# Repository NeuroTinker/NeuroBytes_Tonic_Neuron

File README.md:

# NeuroBytes Tonic Neuron

The NeuroBytes Tonic Neuron is an open-source hardware neuron simulator designed and sold by [NeuroTinker, LLC](http://www.neurotinker.com/). 

All NeuroBytes products are based on the ST32L0x series of ARM Cortex-M0+ 32-bit microcontrollers. The boards were designed in KiCad and Inkscape and are released under the terms of the Creative Commons Attribution-ShareAlike 4.0 license, available here: http://creativecommons.org/licenses/by-sa/4.0/. The NeuroBytes Tonic Neuron is Certified Open Source Hardware as defined by [OSHWA](https://www.oshwa.org), certification number US000112.

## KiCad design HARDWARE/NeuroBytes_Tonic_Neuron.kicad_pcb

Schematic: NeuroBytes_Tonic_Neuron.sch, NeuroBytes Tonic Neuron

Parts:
C1, C4: 1u; C_0603_HandSoldering; Mfr Part # LMK107B7105KA-T
C2: 10u; C_1206; Mfr Part # EMK316B7106KL-TD
C3, C5: 0u1; ZF_SMD_NonPol_0402_cap; Mfr Part # LMK105BJ104KV-F
D1: LED_RABG; ZF_LED_RGB_SunLED_XZMDKCBDDG45S-9_cast; Mfr Part # XZMDKCBDDG45S-9
P1, P2, P3: CONN_01X04; ZF_CONN_JST_GH; Mfr Part # SM04B-GHS-TB(LF)(SN)
P4: JST_GH_5-pos; ZF_CONN_JST_GH_5POS; Mfr Part # SM05B-GHS-TB(LF)(SN)
Q1, Q2, Q3: Q_NPN_BEC; ZF_SOT23-3L; Mfr Part # MMBT3904-TP
R1: 150; ZF_SMD_NonPol_0402; Mfr Part # RC0402FR-07150RL
R2, R3: 470k; ZF_SMD_NonPol_0402; Mfr Part # RC0402FR-07470KL
R4: JMP; ZF_SMD_NonPol_0402; Mfr Part # RC0402JR-070RL
R5, R6: 100; ZF_SMD_NonPol_0402; Mfr Part # RC0402FR-07100RL
R7, R8, R9: 1k; ZF_SMD_NonPol_0402; Mfr Part # RC0402FR-071KL
SW1: SW_PUSH; ZF_SW_Momentary_SideMtg; Mfr Part # TL3330AF130QG
TP3, TP4: TEST; ZF_CONN_1-2_pad
U1: STM32L011Gx; ZF_IC_UFQFPN28-050; Mfr Part # STM32L011G4U6
U2: TLV70033_SOT23-5; ZF_SOT23-5L; Mfr Part # NCP114BSN330T1G
U3: RClamp0503F; ZF_SMD_SOT-353; Mfr Part # RCLAMP0503F.TCT

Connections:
+3V3: C2.1, C3.1, C4.1, U1.5 (VDDA), U1.17 (VDD), U2.5, U3.5
+5V: C1.1, D1.2 (A), P1.2, P2.2, P3.2, P4.5, U2.1, U2.3
A1EX: P2.4, U1.12 (PA6_5V)
A1IN: P2.3, U1.11 (PA5_3V3/TIM2_CH1)
A2EX: P3.4, U1.14 (PB0_5V/TIM2_CH2/3)
A2IN: P3.3, U1.13 (PA7_5V/MOSI)
D1EX: P1.4, U1.25 (PB4_5V)
D1IN: P1.3, U1.24 (PB3_5V/TIM2_CH2)
GND: C1.2, C2.2, C3.2, C4.2, C5.2, P1.1, P2.1, P3.1, P4.1, Q1.2, Q2.2, Q3.2, R4.1, SW1.1, U1.16 (VSS), U2.2, U3.2
LED_B: R9.2, U1.8 (PA2_3V3/TIM2_CH3/TIM21_CH1)
LED_G: R8.2, U1.6 (PA0_3V3/TIM2_CH1)
LED_R: R7.2, U1.7 (PA1_5V/TIM2_CH2)
unnamed: D1.1 (RK), R1.1
unnamed: D1.3 (BK), R6.1
unnamed: D1.4 (GK), R5.1
unnamed: Q1.1, R7.1
unnamed: Q1.3, R1.2
unnamed: Q2.1, R8.1
unnamed: Q2.3, R5.2
unnamed: Q3.1, R9.1
unnamed: Q3.3, R6.2
unnamed: R2.1, TP4.1, U1.19 (PA9_5V/TIM21_CH2), U3.1
unnamed: R2.2, U1.15 (PB1_5V/MOSI/TIM2_CH4)
unnamed: R3.1, TP3.1, U1.20 (PA10_5V/TIM21_CH1), U3.3
unnamed: R3.2, U1.18 (PA8_5V/TIM2_CH1)
unnamed: R4.2, U1.1 (BOOT)
unnamed: SW1.2, U1.28 (PB7_5V/TIM2_CH4), U3.4
RESET: C5.1, P4.2, U1.4 (NRST)
SWCLK: P4.4, U1.22 (PA14/SWCLK/MISO)
SWDIO: P4.3, U1.21 (PA13/SWDIO/SCK)

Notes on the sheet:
MICROCONTROLLER
BYPASS CAPS
DENDRITE
POWER SUPPLY
POWER/PROGRAMMING CONNECTOR
LED
AXON TERMINAL

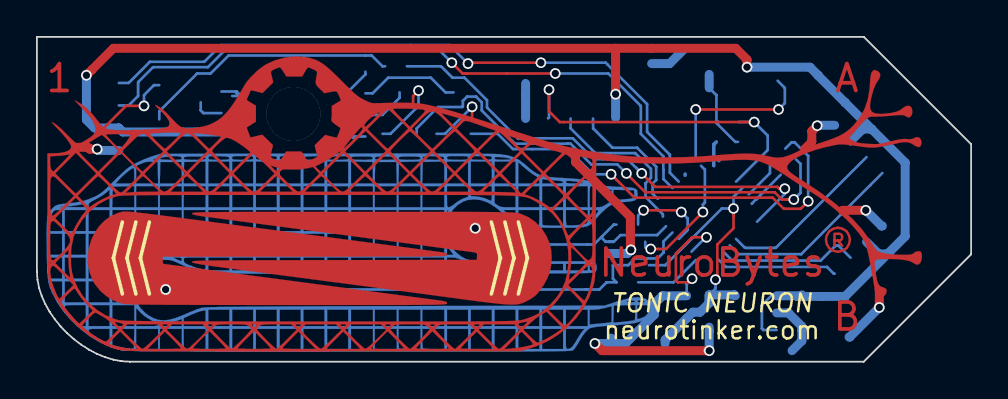
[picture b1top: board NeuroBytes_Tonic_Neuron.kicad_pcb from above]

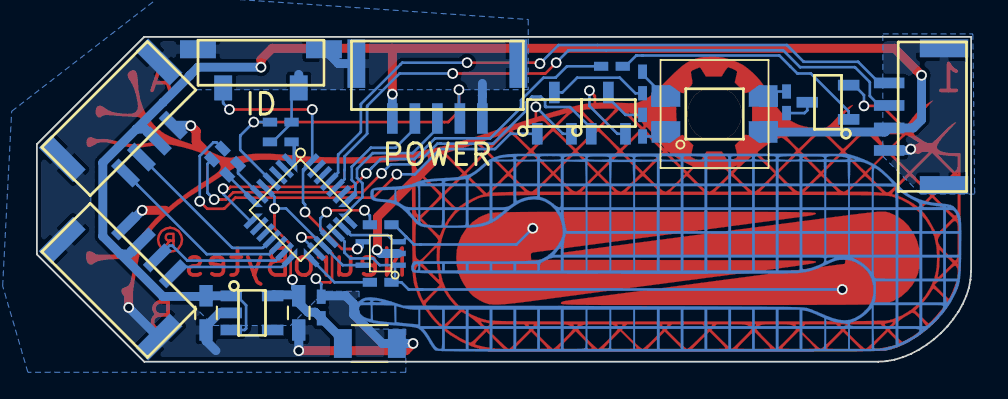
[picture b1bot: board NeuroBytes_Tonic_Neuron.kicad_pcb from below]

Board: 2 copper layers, 51.9 x 18.0 mm, 28 parts (26 on the bottom side), 30 nets.

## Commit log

2017-05-18 Initial commit. Pulled in libopencm3 and Schematic_Lib libraries. First PCB spin (not yet tested!).
2017-05-18 Add existing files to NT repo
2017-05-19 First commit of new firmware. LED seems to work and the chip isn't fried. No touch sensor or serial stuff yet.
2017-05-19 Trying to write an STM32L0 USART driver. doesn't work yet.
2017-05-19 Got basic USART functionality working following libopencm3 STM32Fx templates and examples. Implemented mini-printf from https://github.com/mludvig/mini-printf (as normal printf is too heavy). Test pr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
2017-05-19 Moved mini-printf readme file to main directory (and renamed)
2017-05-19 Additional touch sensor tests. Not working with gpio_get() function. Need to try pin change interrupts.
2017-05-23 Got a 3-bit resolution touch slider demo working using TIM21 capture inputs. Fades the LED with position and outputs raw value over USART2.
2017-05-26 save test code and start neuron
2017-05-26 testing wait period
2017-05-30 made code non-blocking
2017-05-30 added sliding accumulator
2017-05-30 added neuron and communication functionality
2017-06-01 cleaned up tests
2017-06-29 fresh clone with current firmware. added new PCB design -- bipolar neuron graphics, etc.
2017-07-08 removed miniprintf stuff. updated firmware for new board with external resistors for touch slider. currently runs test program that maps finger position to blue LED color.
2017-07-19 fixed dendrite bug
2017-07-19 fixed dendrite
2017-08-11 reorganized
2017-08-11 added elf
2017-08-11 changed to 5-pin JST GH connector for power / prog
2017-08-11 changed fingerprint address
2017-08-11 changed fingerprint
2017-08-11 add elf
2017-08-28 added kicad text to *.svg. added *.png export of board front.
2017-09-06 illustration updates
2017-09-06 fresh *.png exports
2017-09-06 create readme.md w/ pcb render image
2017-09-11 fixed simultaneous exciation issue
2017-09-11 made elf
2017-09-11 added antialiasing
2017-09-20 updated graphics file to match master
2017-09-22 added .gitignore. cleaned up .fingerprint
2017-09-22 enforced .gitignore
2017-09-23 changed to single NPN transitors and non-networked resistors. still need to finish routing.
2017-09-25 finished routing with discrete NPN transitors and resistors
2017-10-01 updated BOM labels. missing link and part number for R2 and R3.
2017-10-01 Reloaded netlist. Added notes to F.Fab layer. Generated production files.
2017-10-03 pulled back mask on dendrite and axon terminal labels. other minor PCB updates.
2017-10-03 minor page layout updates
2017-10-04 BOM updates. Regenerated netlist.
2017-10-04 pulled front paste off touch pads
2017-11-28 added neurobytes common
2017-11-30 updated license to CC-BY-SA 4.0. updated readme.md. added drawing no. to PCB.
2017-11-30 PI demo build
2018-01-23 preparing for merge
2018-01-25 use neurobytes core
2018-01-25 fixed bugs with comms
2018-01-25 fixed LED
2018-01-25 reorganize
2018-01-31 switched to old pinout
2018-01-31 fixed for old pinout
2018-01-31 changed to RClamp0503F for ESD protection (touch slider, switch, 3v3). ordered 30 PCBs.
2018-02-23 added pause/play. made elf
2018-03-08 updated ESD protection stuff. minor PCB render updates.
2018-03-08 added OSHWA cert logo to README.md
2018-04-09 fixed axon 2
2018-04-10 fixed axon2
2018-04-10 fixed weird inhib/excit bug
2018-05-23 generated fab files and BOM
2018-05-23 updated INSERT attribute. regenerated *.pos file.
2018-05-31 added schematic *.pdf
2018-08-06 updated footprints to include B.Fab outlines. minor routing changes. poured ground plane around connectors. re-generated Gerbers. added placement pdf.
2018-08-08 regen Gerbers and drill file
2018-12-29 increased LED brightness
2018-12-29 increased LED brightness for APs

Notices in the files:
HARDWARE/NeuroBytes_Tonic_Neuron.kicad_pcb:
(C) 2017 Zach Fredin
License: CC-BY-SA 4.0
HARDWARE/NeuroBytes_Tonic_Neuron.sch:
(C) 2018 Zach Fredin
